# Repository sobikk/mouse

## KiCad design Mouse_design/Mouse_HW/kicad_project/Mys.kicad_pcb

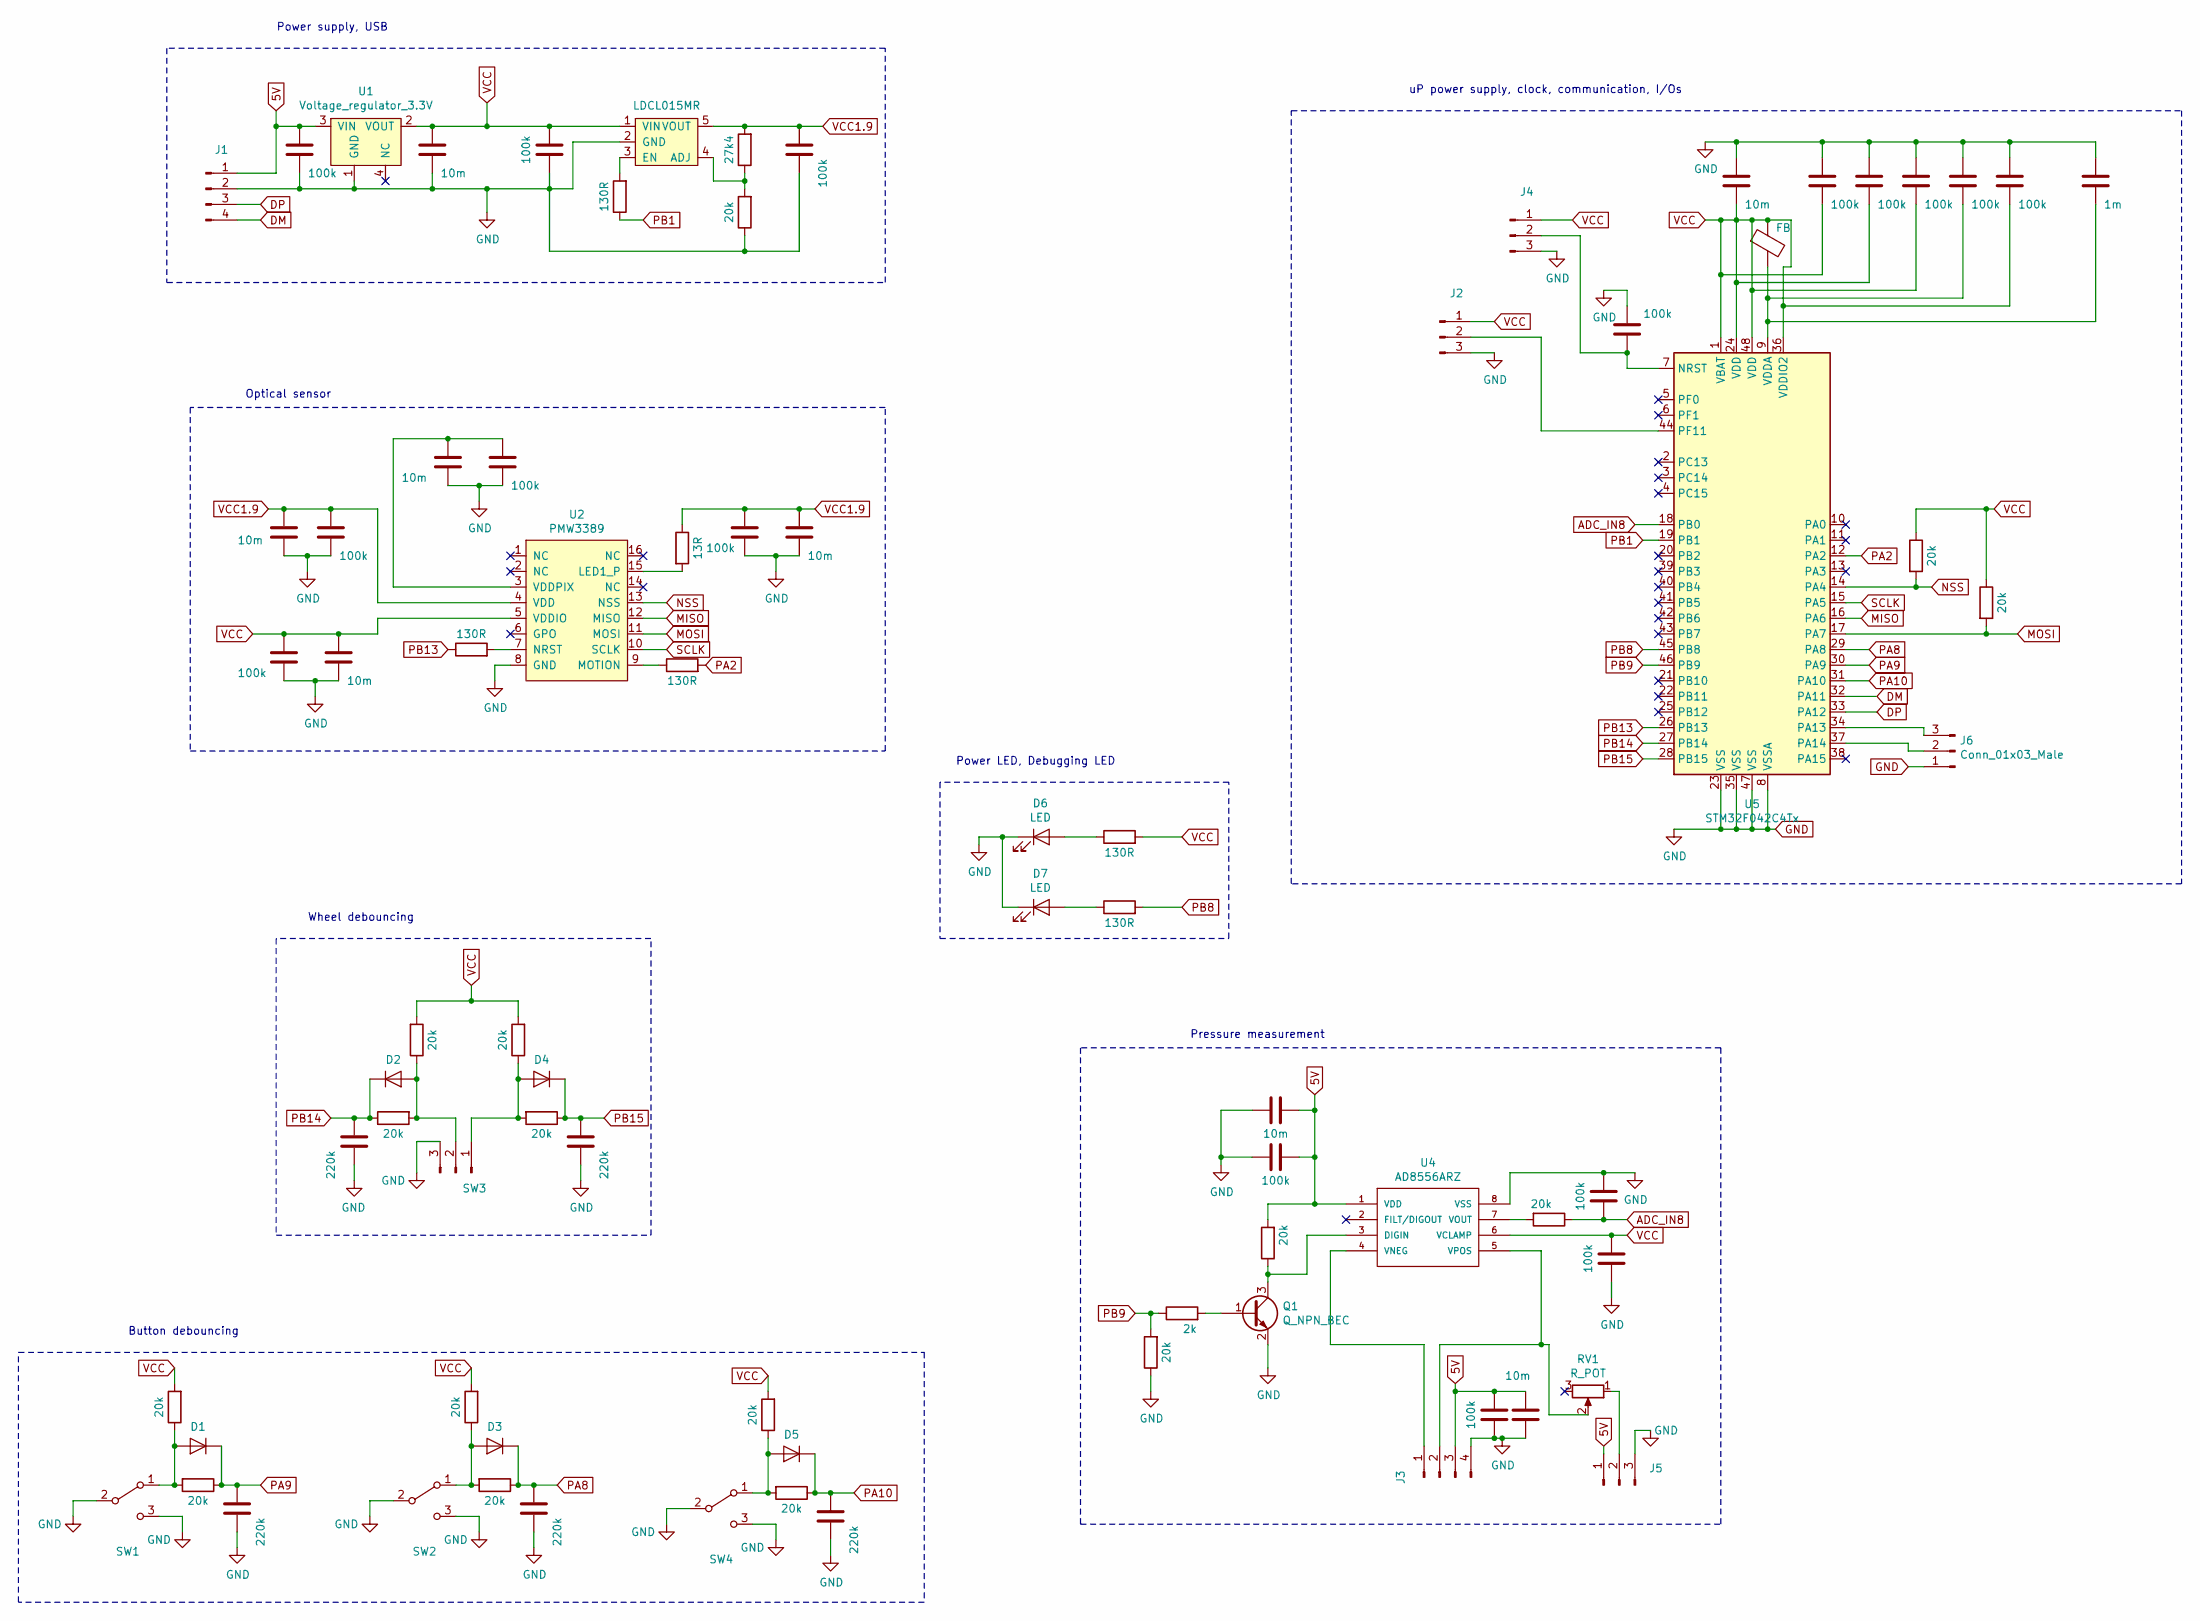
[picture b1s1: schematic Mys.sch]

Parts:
C1, C7, C11, C13, C17: 220k; C_0402_1005Metric
C2, C6, C8, C9, C16, C18, C25, C33: 10m; C_0603_1608Metric_Pad1.05x0.95mm_HandSolder
C3, C4, C5, C10, C12, C14, C15, C19, C22, C23, C24, C26, C27, C28, C29, C30, C32: 100k; C_0402_1005Metric
C31: 1m; C_0603_1608Metric_Pad1.05x0.95mm_HandSolder
D1, D2, D3, D4, D5: D; D_0603_1608Metric_Pad1.05x0.95mm_HandSolder
D6, D7: LED; LED_0603_1608Metric_Pad1.05x0.95mm_HandSolder
FB1: FB; L_0603_1608Metric_Pad1.05x0.95mm_HandSolder
J1: Conn_01x04_Male; NXW-04
J2, J4, J5, J6: Conn_01x03_Male; PinHeader_1x03_P2.00mm_Vertical
J3: Conn_01x04_Male; PinHeader_1x04_P2.00mm_Vertical
Q1: Q_NPN_BEC; SOT-23
R1, R2, R3, R4, R6, R7, R8, R9, R14, R15, R16, R19, R21, R23, R24, R25: 20k; R_0402_1005Metric
R5, R10, R12, R17, R18: 130R; R_0603_1608Metric_Pad1.05x0.95mm_HandSolder
R11: 13R; R_0603_1608Metric_Pad1.05x0.95mm_HandSolder
R13: 27k4; R_0402_1005Metric
R20: 2k; R_0402_1005Metric
RV1: R_POT; Potentiometer_Bourns_3214J_Horizontal
SW1, SW2, SW4: SW_SPDT; Button_mouse
SW3: Conn_01x03_Male; Encoder
U1: Voltage_regulator_3.3V; SOT-223
U2: PMW3389; PMW3389DM-T3QU
U3: LDCL015MR; SOT-23-5_HandSoldering
U4: AD8556ARZ; SOIC-8_3.9x4.9mm_P1.27mm
U5: STM32F042C4Tx; LQFP-48_7x7mm_P0.5mm

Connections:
5V: C4.2, C18.2, C19.2, C32.2, C33.2, J1.1, J3.3, J5.1, R21.2, U1.3 (VIN), U4.1 (VDD)
ADC_IN8: C22.2, R23.1, U5.18 (PB0)
DM: J1.4, U5.32 (PA11)
DP: J1.3, U5.33 (PA12)
GND: C1.1, C2.1, C3.1, C4.1, C5.1, C6.1, C7.1, C8.1, C9.1, C10.1, C11.1, C12.1, C13.1, C14.1, C15.1, C16.1, C17.1, C18.1, C19.1, C22.1, C23.2, C24.2, C25.2, C26.2, C27.2, C28.2, C29.2, C30.2, C31.2, C32.1, C33.1, D6.1 (K), D7.1 (K), J1.2, J2.3, J3.4, J4.3, J5.3, J6.1, Q1.2 (E), R14.1, R19.1, SW1.2 (B), SW1.3 (C), SW2.2 (B), SW2.3 (C), SW3.3, SW4.2 (B), SW4.3 (C), U1.1 (GND), U2.8 (GND), U3.2 (GND), U4.8 (VSS), U5.8 (VSSA), U5.23 (VSS), U5.35 (VSS), U5.47 (VSS)
MISO: U2.12 (MISO), U5.16 (PA6)
MOSI: R25.2, U2.11 (MOSI), U5.17 (PA7)
NSS: R24.2, U2.13 (NSS), U5.14 (PA4)
unnamed: C9.2, C10.2, U2.3 (VDDPIX)
unnamed: C24.1, J4.2, U5.7 (NRST)
unnamed: C29.1, C31.1, FB1.2, U5.9 (VDDA)
unnamed: D1.2 (A), R1.1, R2.2, SW1.1 (A)
unnamed: D2.2 (A), R3.2, R4.1, SW3.2
unnamed: D3.2 (A), R6.1, R7.2, SW2.1 (A)
unnamed: D4.2 (A), R8.1, R9.2, SW3.1
unnamed: D5.2 (A), R15.1, R16.2, SW4.1 (A)
unnamed: D6.2 (A), R17.1
unnamed: D7.2 (A), R18.1
unnamed: J2.2, U5.44 (PF11)
unnamed: J3.1, U4.4 (VNEG)
unnamed: J3.2, RV1.2, U4.5 (VPOS)
unnamed: J5.2, RV1.1
unnamed: J6.2, U5.37 (PA14)
unnamed: J6.3, U5.34 (PA13)
unnamed: Q1.1 (B), R20.2
unnamed: Q1.3 (C), R21.1, U4.3 (DIGIN)
unnamed: R5.2, U2.7 (NRST)
unnamed: R10.2, U3.3 (EN)
unnamed: R11.2, U2.15 (LED1_P)
unnamed: R12.1, U2.9 (MOTION)
unnamed: R13.1, R14.2, U3.4 (ADJ)
unnamed: R23.2, U4.7 (VOUT)
PA2: R12.2, U5.12 (PA2)
PA8: C11.2, D3.1 (K), R7.1, U5.29 (PA8)
PA9: C1.2, D1.1 (K), R2.1, U5.30 (PA9)
PA10: C17.2, D5.1 (K), R16.1, U5.31 (PA10)
PB1: R10.1, U5.19 (PB1)
PB8: R18.2, U5.45 (PB8)
PB9: R19.2, R20.1, U5.46 (PB9)
PB13: R5.1, U5.26 (PB13)
PB14: C7.2, D2.1 (K), R3.1, U5.27 (PB14)
PB15: C13.2, D4.1 (K), R9.1, U5.28 (PB15)
SCLK: U2.10 (SCLK), U5.15 (PA5)
VCC: C3.2, C6.2, C8.2, C12.2, C23.1, C25.1, C26.1, C27.1, C28.1, C30.1, FB1.1, J2.1, J4.1, R1.2, R4.2, R6.2, R8.2, R15.2, R17.2, R24.1, R25.1, U1.2 (VOUT), U2.5 (VDDIO), U3.1 (VIN), U4.6 (VCLAMP), U5.1 (VBAT), U5.24 (VDD), U5.36 (VDDIO2), U5.48 (VDD)
VCC1.9: C2.2, C5.2, C14.2, C15.2, C16.2, R11.1, R13.2, U2.4 (VDD), U3.5 (VOUT)

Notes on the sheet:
Button debouncing
Wheel debouncing
Power LED, Debugging LED
Optical sensor
Pressure measurement
Power supply, USB
uP power supply, clock, communication, I/Os

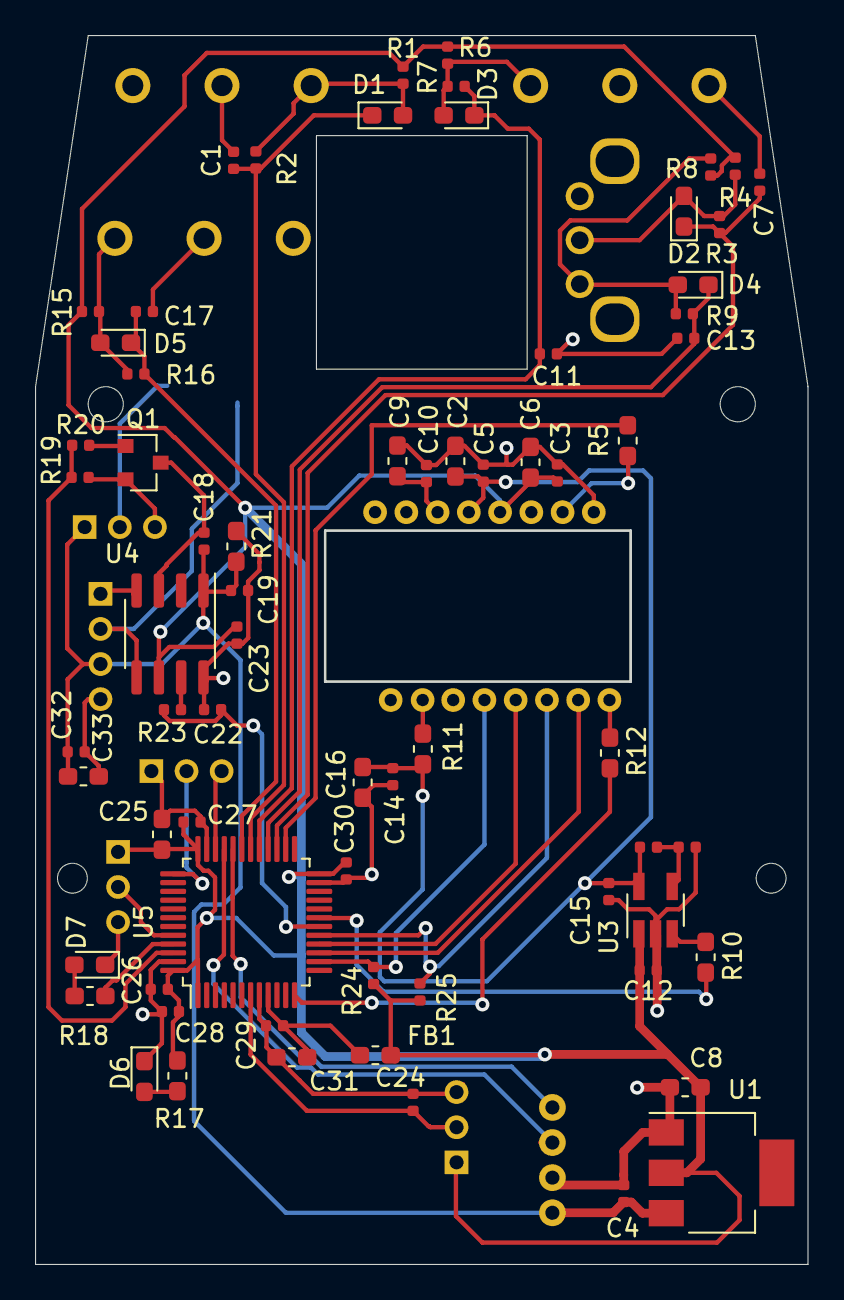
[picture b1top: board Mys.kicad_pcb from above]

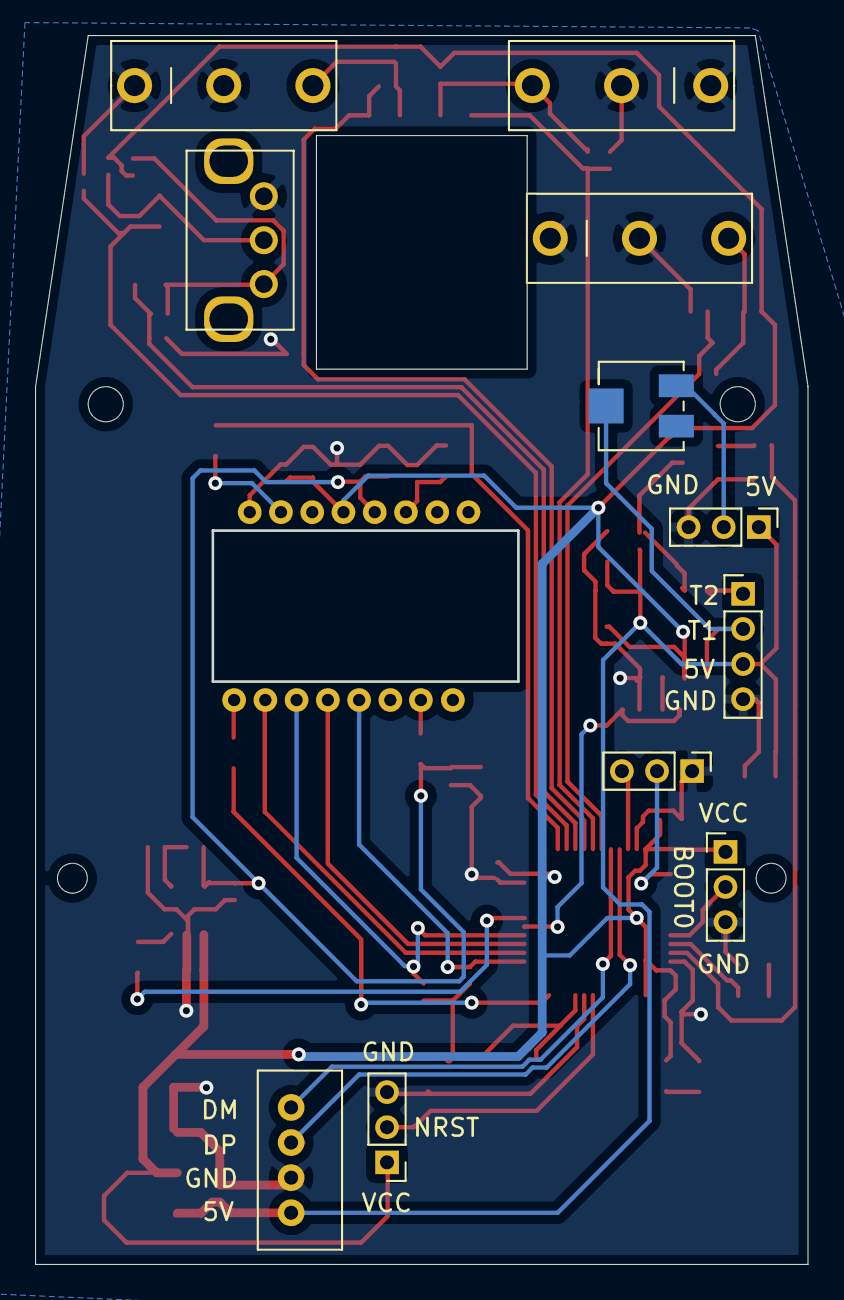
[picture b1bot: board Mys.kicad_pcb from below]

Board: 2 copper layers, 44.0 x 70.0 mm, 80 parts (11 on the bottom side), 45 nets.

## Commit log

2021-01-28 First version - 28_01_2021
